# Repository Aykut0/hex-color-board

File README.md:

# HEX Color Board

A small board that turns real-world colors into HEX codes and back, made as a gift for a graphic-designer friend.

Designers work with colors as HEX codes (like `#E2552C`). The board offers three ways to go between a color and its code: pick a color from the on-screen spectrum and read its code, type a code and see the color, or point the color sensor on the back at anything around you and capture it.

An ESP32-S3-Zero runs the interface on a 2.8-inch SPI touch display. A TCS34725 RGB sensor on the back, read over I²C, has its own white LED for consistent lighting, and a small MOSFET switches the display backlight. The board was made in-house on an LPKF laser PCB machine from the files in `hardware/fabrication/`.

I also designed a case for it in Blender. The board sits on printed pins that pass through its four existing mounting holes, the lid snaps onto the lower tray without screws, the display shows through the front, and a ring on the back gives the color sensor its own shielded window. The module sizes in the model are estimates, so the case still needs a test print before it is final.

| Assembled | Back, with the sensor window |
|---|---|
|  |  |

## Files

```
hardware/                 KiCad project (open hex_display.kicad_pro)
hardware/fabrication/     Gerber and drill files
mechanical/               Blender case model and printable STL shells
docs/images/              renders and schematic
```

The board has been made; photos of the finished board will be added.

---

Yaşar Aykut Altuntop · Koç University · [LinkedIn](https://linkedin.com/in/aykutaltuntop) · [GitHub](https://github.com/Aykut0)

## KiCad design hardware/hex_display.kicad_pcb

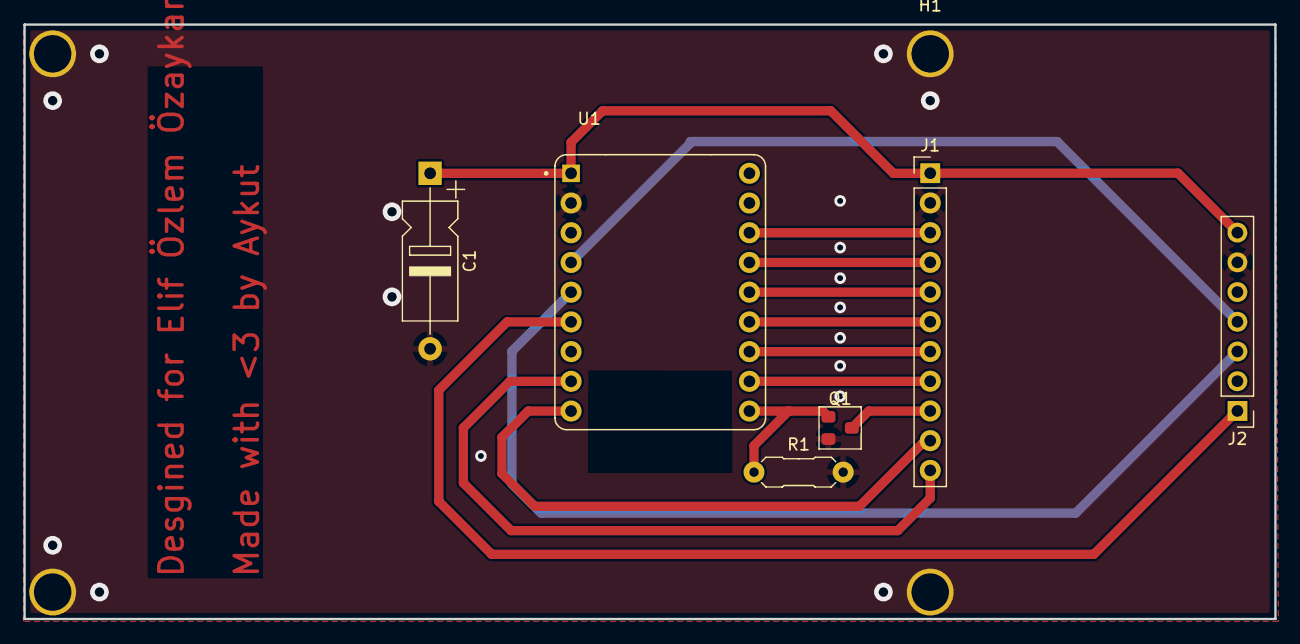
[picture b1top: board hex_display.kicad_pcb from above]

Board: 2 copper layers, 106.9 x 50.8 mm, 7 parts (0 on the bottom side), 15 nets.

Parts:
C1: 100uF; CP_Axial_L10.0mm_D4.5mm_P15.00mm_Horizontal
H1: MountingHole_Pad; MountingHole_3.2mm_M3_Pad_Via
J1: 2.8 inch LCD; PinHeader_1x11_P2.54mm_Vertical
J2: TCS34725; PinHeader_1x07_P2.54mm_Vertical
Q1: AO3400A; SOT-23
R1: 10k; R_Axial_DIN0207_L6.3mm_D2.5mm_P7.62mm_Horizontal
U1: ESP32-S3-ZERO; MODULE_ESP32-S3-ZERO

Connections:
5V: C1.1, J1.1, J2.7, U1.5V
BACKLIGHT_CTRL: Q1.1 (G), R1.1, U1.7 (GP7)
GND: C1.2, H1.1, J1.2, J2.6, Q1.2 (S), R1.2, U1.GND
LCD_BL: J1.9, Q1.3 (D)
LCD_CS: J1.6, U1.10 (GP10)
LCD_DC: J1.7, U1.9 (GP9)
LCD_RST: J1.8, U1.8 (GP8)
LED: J2.1, U1.3 (GP3)
MISO: J1.3, U1.13 (GP13)
MOSI: J1.4, U1.12 (GP12)
SCL: J2.4, U1.1 (GP1)
SCLK: J1.5, U1.11 (GP11)
SDA: J2.3, U1.2 (GP2)
TP_CS: J1.10, U1.6 (GP6)
TP_IRQ: J1.11, U1.5 (GP5)
